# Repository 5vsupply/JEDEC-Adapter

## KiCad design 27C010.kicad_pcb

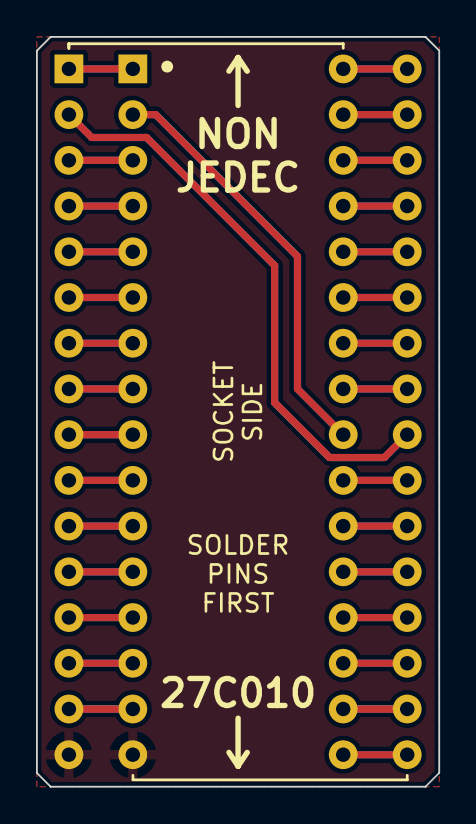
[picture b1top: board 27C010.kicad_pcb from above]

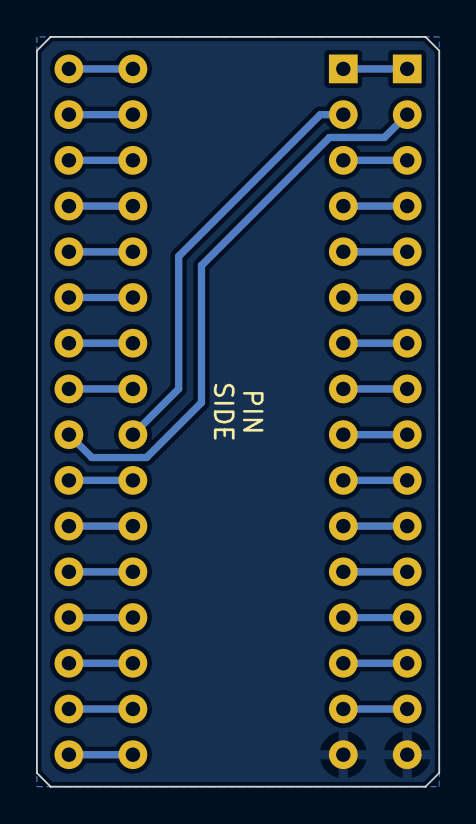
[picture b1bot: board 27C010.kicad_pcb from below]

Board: 2 copper layers, 22.4 x 41.7 mm, 3 parts (2 on the bottom side), 31 nets.

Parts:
J1, J2: Conn_01x16_Male; PinHeader_1x16_P2.54mm_Vertical
U1: TC571001; DIP-32_W15.24mm_Socket

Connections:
/A0: J1.12, U1.12 (A0)
/A1: J1.11, U1.11 (A1)
/A2: J1.10, U1.10 (A2)
/A3: J1.9, U1.9 (A3)
/A4: J1.8, U1.8 (A4)
/A5: J1.7, U1.7 (A5)
/A6: J1.6, U1.6 (A6)
/A7: J1.5, U1.5 (A7)
/A8: J2.27 (Pin_11), U1.27 (A8)
/A9: J2.26 (Pin_10), U1.26 (A9)
/A10: J2.23 (Pin_7), U1.23 (A10)
/A11: J2.25 (Pin_9), U1.25 (A11)
/A12: J1.4, U1.4 (A12)
/A13: J2.28 (Pin_12), U1.28 (A13)
/A14: J2.29 (Pin_13), U1.29 (A14)
/A15: J1.3, U1.3 (A15)
/A16: J1.2, U1.24 (A16)
/D0: J1.13, U1.13 (D0)
/D1: J1.14, U1.14 (D1)
/D2: J1.15, U1.15 (D2)
/D3: J2.17 (Pin_1), U1.17 (D3)
/D4: J2.18 (Pin_2), U1.18 (D4)
/D5: J2.19 (Pin_3), U1.19 (D5)
/D6: J2.20 (Pin_4), U1.20 (D6)
/D7: J2.21 (Pin_5), U1.21 (D7)
/GND: J1.16, U1.16 (GND)
/VCC: J2.32 (Pin_16), U1.32 (VCC)
/VPP: J1.1, U1.1 (VPP)
/~CE: J2.22 (Pin_6), U1.22 (~CE)
/~OE: J2.24 (Pin_8), U1.2 (~OE)
/~PGM: J2.31 (Pin_15), U1.31 (~PGM)

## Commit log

2022-06-25 init
2022-06-25 done
